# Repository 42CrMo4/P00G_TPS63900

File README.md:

# TPS63900

## Goal

The goal of the project will be:
- [ ] **undefined** - not known what the project will bring 
- [ ] **learn** - personally learn something new, no usefull outcome expected
- [x] **prototype** - a working prototype or mvp
- [ ] **80-20-rule** - 80% outcome with 20% effort
- [ ] **Product** - lets see :wink:

## Description. 

| Font                                                                    | Back                                                                      |
|-------------------------------------------------------------------------|---------------------------------------------------------------------------|
|  |  |

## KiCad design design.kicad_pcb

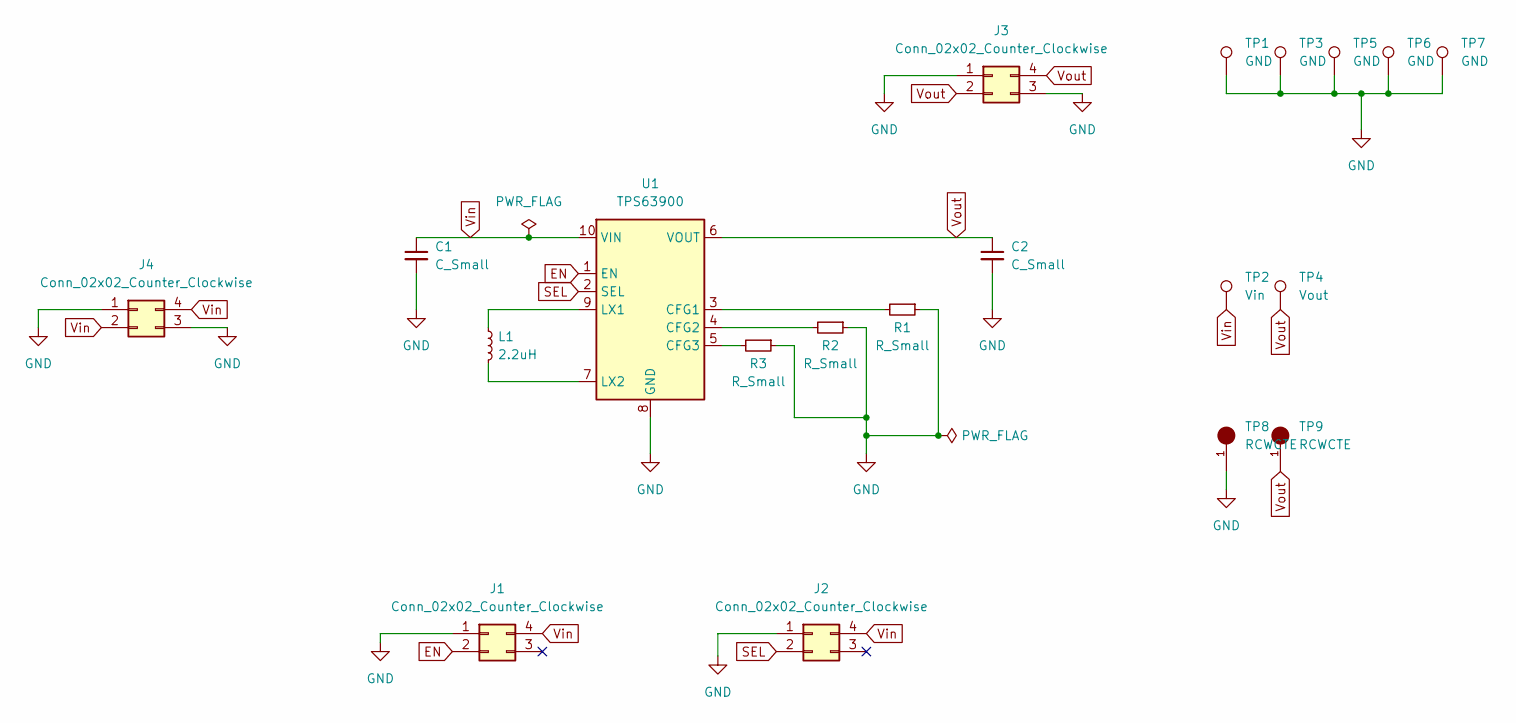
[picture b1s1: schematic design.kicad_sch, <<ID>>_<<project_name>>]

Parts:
C1, C2: C_Small; C_0603_1608Metric
J1, J2, J3, J4: Conn_02x02_Counter_Clockwise; PinSocket_2x02_P2.54mm_Vertical
L1: 2.2uH; L_1008_2520Metric
R1, R2, R3: R_Small; R_0805_2012Metric
TP1, TP3, TP5, TP6, TP7: GND; TestPoint_Pad_D3.0mm
TP2: Vin; TestPoint_Pad_D3.0mm
TP4: Vout; TestPoint_Pad_D3.0mm
TP8, TP9: RCWCTE; RCWCTE_TP420X150; PARTREV 1/06/14
U1: TPS63900; WSON-10-1EP_2.5x2.5mm_P0.5mm_EP1.2x2mm_ThermalVias

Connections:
EN: J1.2, U1.1 (EN)
GND: C1.2, C2.2, J1.1, J2.1, J3.1, J3.3, J4.1, J4.3, R1.1, R2.1, R3.1, TP1.1, TP3.1, TP5.1, TP6.1, TP7.1, TP8.1, U1.8 (GND), U1.11 (GND)
unnamed: L1.1, U1.9 (LX1)
unnamed: L1.2, U1.7 (LX2)
unnamed: R1.2, U1.3 (CFG1)
unnamed: R2.2, U1.4 (CFG2)
unnamed: R3.2, U1.5 (CFG3)
SEL: J2.2, U1.2 (SEL)
Vin: C1.1, J1.4, J2.4, J4.2, J4.4, TP2.1, U1.10 (VIN)
Vout: C2.1, J3.2, J3.4, TP4.1, TP9.1, U1.6 (VOUT)

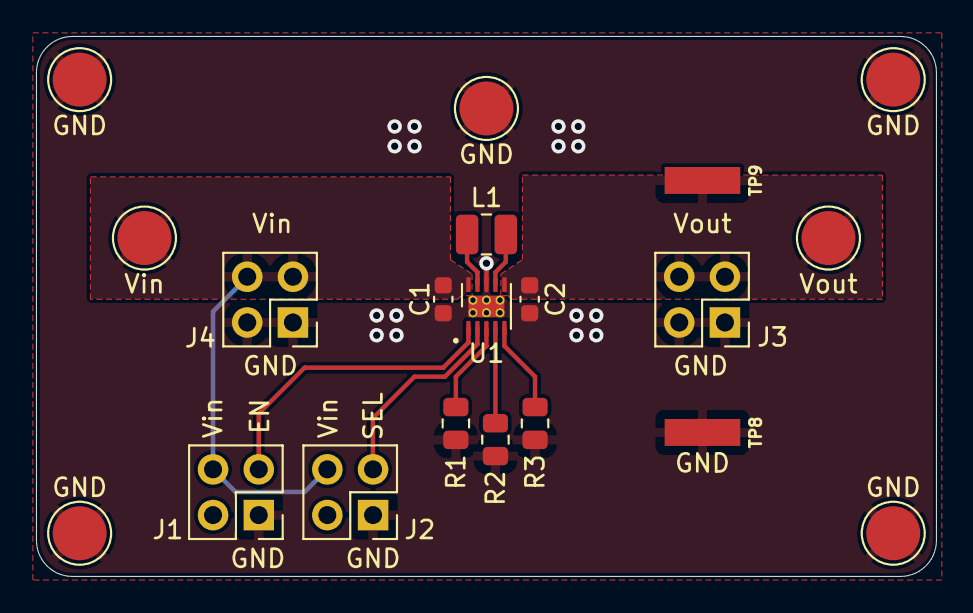
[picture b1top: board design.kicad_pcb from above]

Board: 2 copper layers, 50.0 x 30.0 mm, 20 parts (0 on the bottom side), 10 nets.

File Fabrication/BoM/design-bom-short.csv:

Row,Description,Part,References,Value,Footprint,Quantity Per PCB,Status,Datasheet,PARTREV,SNAPEDA_PN,MANUFACTURER,MAXIMUM_PACKAGE_HEIGHT,STANDARD
1,"Unpolarized capacitor, small symbol",C_Small,C1 C2,C_Small,C_0603_1608Metric,2, ,~,,,,,
2,"Generic connector, double row, 02x02, counter clockwise pin numbering scheme (similar to DIP package numbering), script generated (kicad-library-utils/schlib/autogen/connector/)",Conn_02x02_Counter_Clockwise,J1 J2 J3 J4,Conn_02x02_Counter_Clockwise,PinSocket_2x02_P2.54mm_Vertical,4, ,~,,,,,
3,"Inductor, small symbol",L_Small,L1,2.2uH,L_1008_2520Metric,1, ,~,,,,,
4,"Resistor, small symbol",R_Small,R1 R2 R3,R_Small,R_0805_2012Metric,3, ,~,,,,,
5,"Buck-Boost Converter, 1.8-5.5V Input Voltage, 0.4A Switch Current, Adjustable 1.8-5V Output Voltage, WSON-10",TPS63900,U1,TPS63900,WSON-10-1EP_2.5x2.5mm_P0.5mm_EP1.2x2mm_ThermalVias,1, ,https://www.ti.com/lit/ds/symlink/tps63900.pdf,,,,,

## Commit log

2025-01-22 DEL template stuff
2025-01-22 DEL template
2025-01-25 add power flags
2025-01-25 make tps63900 vias bigger
    may be not in spec.
2025-01-25 Update Bom and PCB_top
2025-01-25 Archive & Renew release docs
